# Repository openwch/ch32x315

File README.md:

# RISC-V core industrial-grade multi-channel ADC microcontroller CH32X315
EN | [中文](README_zh.md)

### Overview

CH32X315 is a multi-channel ADC microcontroller designed based on the Tibetan barley RISC-V core. The core supports 480MHz zero-wait operation and supports single-precision floating-point instructions and bit manipulation instructions. CH32X315 has four sets of high-speed 12-bit ADC conversion units built-in, providing 48 direct inputs
The channel supports scanning mode and can be expanded to 8 times the number of channels with an analog switch chip, which can automatically switch. It is equipped with a built-in USB 3.0 ultra-high-speed controller and PHY, a USB 2.0 high-speed controller and PHY, as well as a Type-C/PD controller and PHY. It supports USB 3.2 Gen1 and USBSS Device
Equipment functions, USBHS Host and USBHS Device functions, Type-C and PDUSB fast charging functions; provides rich peripheral resources such as DMA controller, ARGB single-wire RGB driver, multiple sets of timers, 4 sets of USART serial ports, 2 sets of I2C interfaces, 3 sets of SPI, etc.
CH32X305 has the USB 3.0 module removed from CH32X315.

### System Block Diagram

### Features

- Qingke 32-bit RISC-V3F core, with multiple instruction set combinations
- Fast programmable interrupt controller + hardware interrupt stack
- Level 2 interrupt nesting
- Supports single-precision floating-point instructions and bit manipulation instructions
- The highest frequency of the kernel is 480MHz, and the highest frequency of the system is 313MHz
- In performance mode, the kernel supports 625MHz, and the system supports 400MHz

- 64KB volatile data storage area SRAM
- 480KB program storage area CodeFlash
(192KB zero-wait application area + 288KB non-zero-wait data area)
- 28KB system bootloader storage area for BootLoader
- 128B user-defined information storage area

- System power supply VDD range: 2.8~3.6V
- Low power consumption modes: sleep, stop

- Built-in factory-calibrated 20MHz RC oscillator
- Built-in RC oscillator with a frequency of approximately 40kHz
- High-speed oscillator supports external 5~32MHz crystal
- Power-on/off reset, programmable voltage monitor

- One 16-bit advanced timer, supporting dead zone control and emergency braking
Vehicle, providing complementary PWM output for motor control
- 2 general-purpose 16-bit timers and 1 general-purpose 32-bit timer, providing input capture
Capture/output comparison/PWM/pulse counting and incremental encoder input
- 2 watchdog timers (independent and window type)
- System time base timer: 32-bit counter

- Real-Time Clock (RTC): 32-bit independent timer

- 11 DMA channels, supporting ring buffer management

- 4 sets of 12-bit analog-to-digital converters (ADCs):
- Analog input range: VREF- to VREF+
- 4*12=48 external signal channels + 1 internal signal channel
- Sampling rate up to 5Msps, supporting multiple ADC conversion modes
- Supports scanning mode and automatic switching with external extensions
- Support for early channel switching to facilitate stable signal sampling
- Supports 4 sets of ADC cascading, equivalent to a 20Msps sampling rate

- 4 sets of USART serial ports: support LIN

- 2 sets of I2C interfaces

- 3 sets of SPI interfaces

- 5Gbps ultra-high-speed USB 3.0 controller and PHY
- Supports ultra-high-speed Device mode
- High-speed integrated design, with a measured speed of 450 Mbytes per second

- 480Mbps high-speed USB 2.0 controller and PHY:
- Supports high-speed/full-speed Host and Device modes
- Supports 1024-byte data packets

- USB PD and Type-C controller and PHY:
- Supports DRP, Sink, and Source applications, as well as PDUSB
- Supports PD3.2 and EPR, and supports 100W or 240W fast charging

- Cascadable and addressable single-wire RGB (ARGB)

- Fast GPIO port:
- 64 I/O ports, mapped to 16 external interrupts

- CRC calculation unit, 96-bit unique chip ID

- Supports both single-line and dual-line debugging modes

- Packaging type: LQFP, QFN

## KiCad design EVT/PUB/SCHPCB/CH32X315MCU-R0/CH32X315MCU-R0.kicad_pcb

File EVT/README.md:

# EVT

### -- download URL
*  CH32X315EVT.ZIP-https://www.wch.cn/downloads/CH32X315EVT_ZIP.html

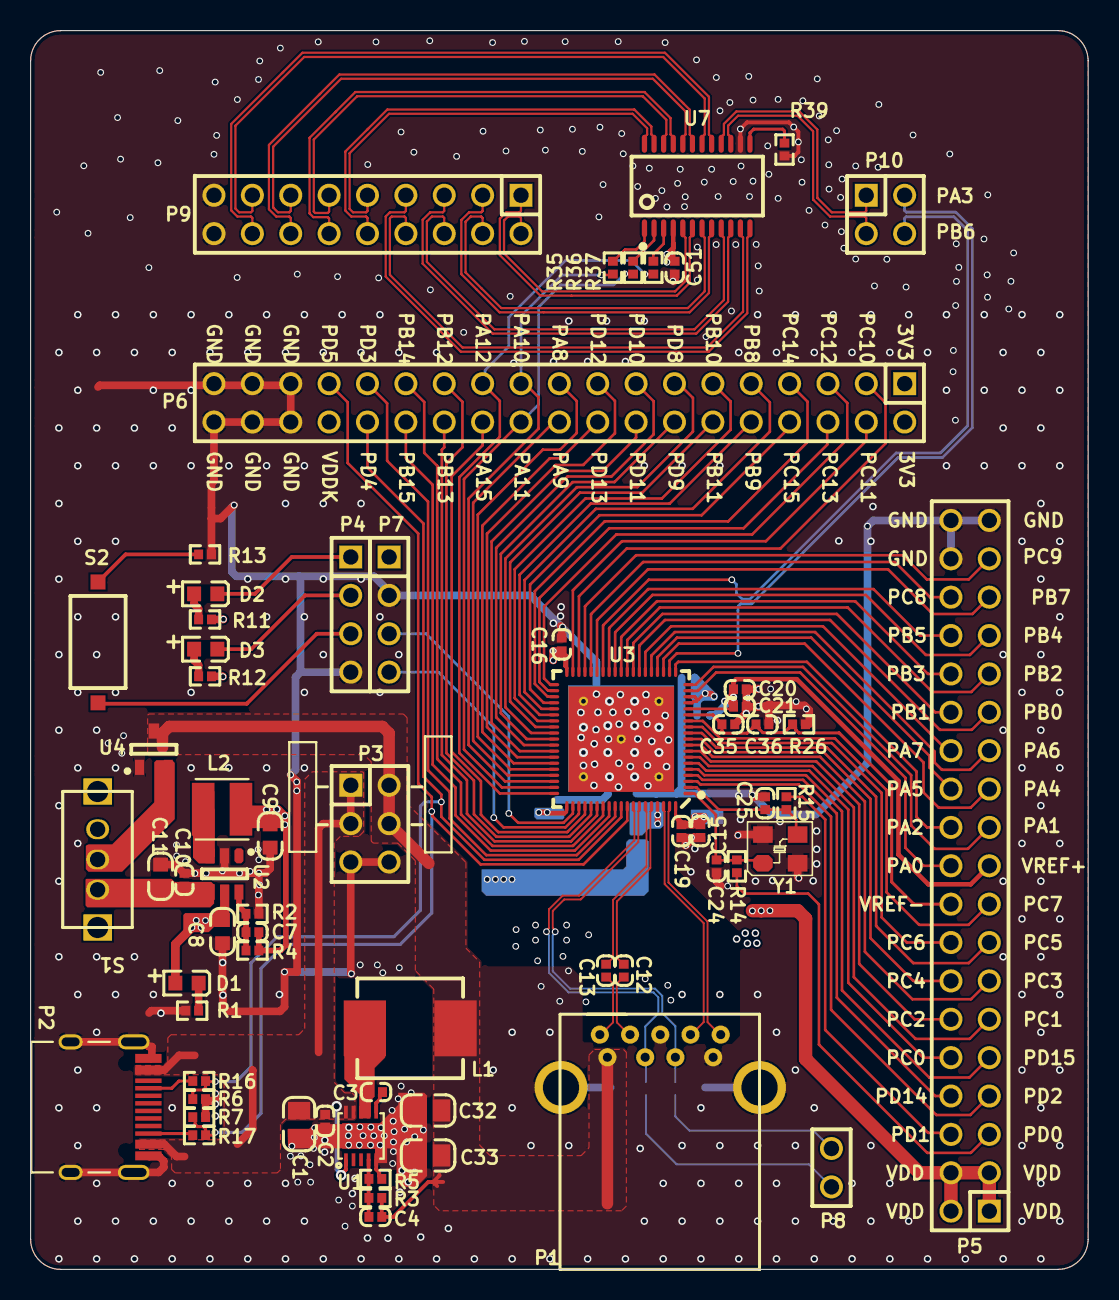
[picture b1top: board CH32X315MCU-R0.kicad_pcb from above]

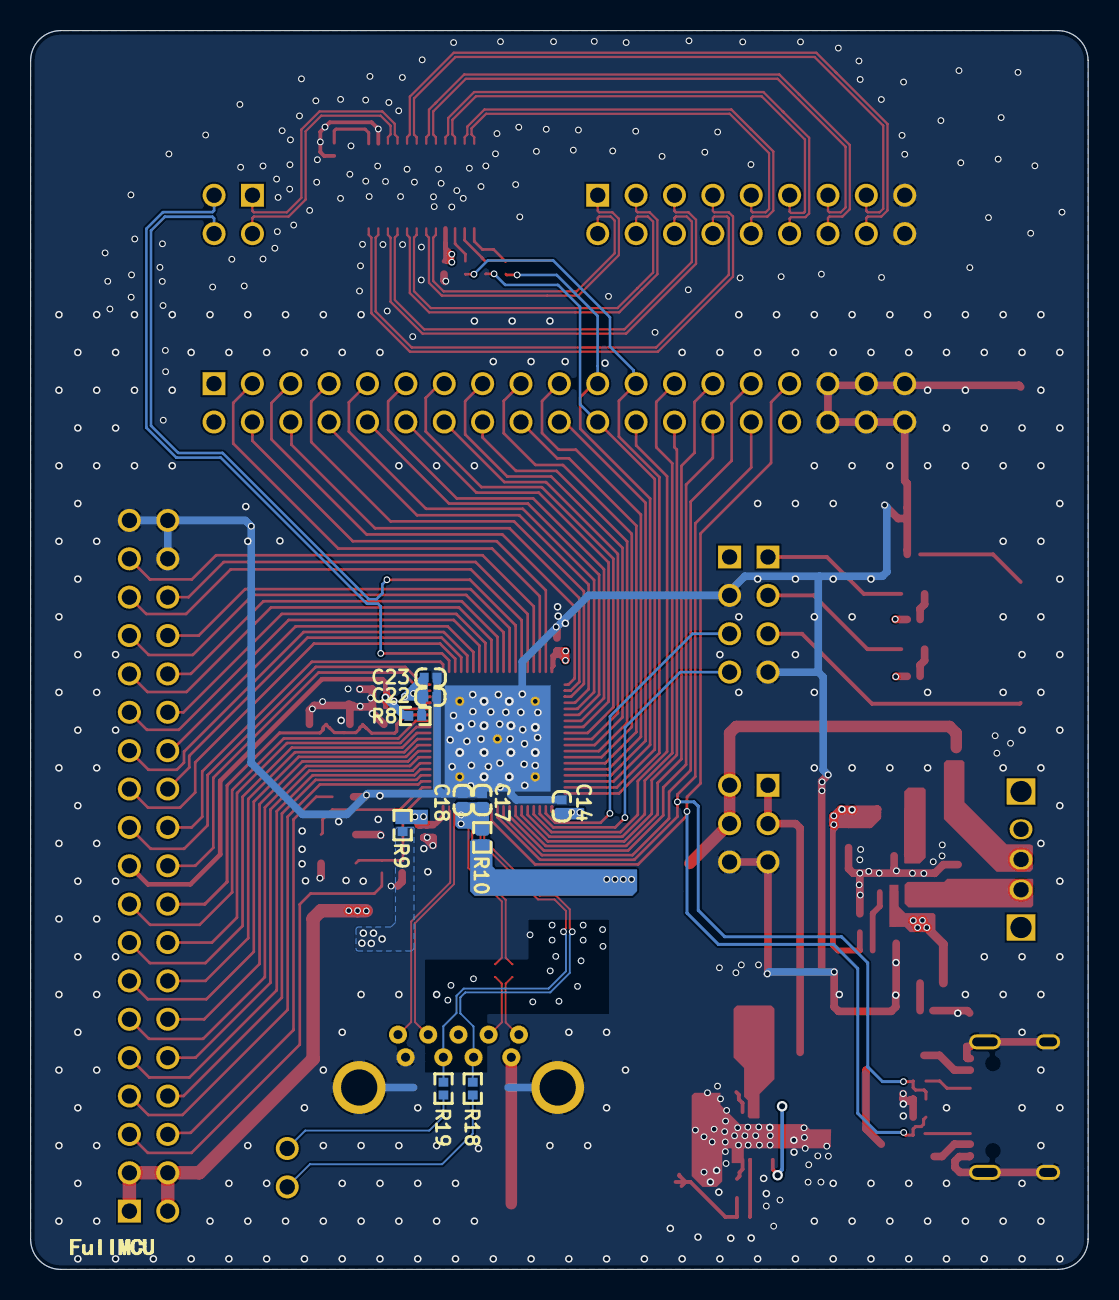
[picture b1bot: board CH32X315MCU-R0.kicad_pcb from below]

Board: 4 copper layers, 70.0 x 82.0 mm, 75 parts (10 on the bottom side), 121 nets.

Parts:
C1: NC(22uF/35V); 0805_C
C2: NC(0.1uF); 0402_C
C3: NC(100nF); 0402_C
C4: NC(68pF); 0402_C
C7: NC(4.7pF); 0402_C
C8, C11: 10uF; 0603_C
C9: NC(10uF); 0603_C
C10, C21, C51: 1uF; 0402_C
C12, C13, C14, C16, C18, C19, C22, C23: 0.1uF; 0402_C
C15: 4.7uF; 0402_C
C17: 2.2uF; 0402_C
C20: 0.01uF; 0402_C
C24, C25: 20pF; 0402_C
C32, C33: NC(22uF); 0805_C
C35: NC(0.01uF); 0402_C
C36: NC(1uF); 0402_C
D1, D3: RED; 0603+
D2: BLUE; 0603+
L1: NC(4.7uH/5A); IND-SMD_L7.0-W6.6
L2: NC(2.2uH); CD32
P1: USB3.0-A; USB3.0-A-Receptacle
P2: TYPE-C; TYPE-C-Receptacle-2.0
P3: HEADER 3x2; IDC6-2.54mm
P4, P7: HEADER 4; SIP4-2.54mm
P5, P6: HEADER 19x2; IDC38-2.54MM
P8: HEADER 2; SIP2-2.54mm
P9: HEADER 9x2; IDC18-2.54MM
P10: Header 2X2; IDC4-2.54mm
R1, R11, R12: 1K; 0402
R2, R4: NC(200k); 0402
R3: NC(15k); 0402
R5: NC(4.7k); 0402
R6, R7: NC(5.1K); 0402
R8, R9, R26: 0R; 0402
R10: NC(0R); 0402
R13: 10K; 0402
R14, R15, R16, R17, R18, R19, R35, R36, R37: NC(0Ω); 0402
R39: 0Ω; 0402
S1: SW SPDT; SW1
S2: KEY; SMD_6.1x3.65x2.5mm-KEY
U1: NC(CH2024Q); DFN10_3X3
U2: CH2003K; SOT-23-6
U3: CH32X315MCU; QFN76_9X9
U4: CH213; SOT-23-3
U7: CH448U; QSOP24
Y1: 20M; XT3225

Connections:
1V2: C7.1, C9.2, L2.2, R4.1, R10.2
3V3: C8.2, D1.1, P6.1, P6.2, P7.1, R9.1, U2.5
+5V: C10.2, C11.2, S1.3, U2.4
A0_X: P9.1, U7.6
A0_Y: P9.2, U7.5
A1_X: P9.3, U7.8
A1_Y: P9.4, U7.7
A2_X: P9.5, U7.10
A2_Y: P9.6, U7.9
A3_X: P9.7, U7.12
A3_Y: P9.8, U7.11
A4_X: P9.9, U7.24
A4_Y: P9.10, U7.23
A5_X: P9.11, U7.22
A5_Y: P9.12, U7.21
A6_X: P9.13, U7.20
A6_Y: P9.14, U7.19
A7_X: P9.15, U7.18
A7_Y: P9.16, U7.17
A_X: P10.1, U7.16
A_Y: P10.3, U7.15
CC1: P6.30, R6.1, R16.2, U3.67
CC2: P6.31, R7.1, R17.2, U3.68
EN#: R39.2, U7.13
FB: C4.2, R3.1, R5.2, U1.4
GND: C1.1, C2.1, C8.1, C9.1, C10.1, C11.1, C14.2, C15.2, C16.1, C17.2, C18.2, C19.2, C20.2, C21.2, C22.2, C23.2, C24.2, C25.2, C32.1, C33.1, C35.2, C36.2, C51.2, P1.0, P1.4, P1.7, P2.0, P2.A1, P2.B1, P3.5, P3.6, P4.4, P5.36, P5.37, P5.38, P6.33, P6.34, P6.35, P6.36, P6.37, P6.38, P7.2, P9.17, P9.18, R1.2, R2.2, R5.1, R6.2, R7.2, R13.1, R26.1, R39.1, U1.0, U1.5, U2.2, U3.0, U4.1, U7.14, Y1.2, Y1.4
KEY: P4.3, S2.1
LED1: D2.2, P4.1
LED2: D3.2, P4.2
NetC3_1: C3.1, U1.6
NetC3_2: C3.2, L1.1, U1.7, U1.8
NetC7_2: C7.2, R2.1, R4.2, U2.6
NetC12_1: C12.1, P1.8
NetC13_1: C13.1, P1.9
NetD1_2: D1.2, R1.1
NetD2_1: D2.1, R11.2
NetD3_1: D3.1, R12.2
NetL2_1: L2.1, U2.3
NetP2_A5: P2.A5, R16.1
NetP2_B5: P2.B5, R17.1
NetR13_2: R13.2, S2.2
NetS1_1: S1.1, U4.2
PA0: P5.20, U3.18
PA1: P5.21, U3.19
PA2: P5.22, U3.20
PA3: P10.2, U3.21
PA4: P5.23, U3.22
PA5: P5.24, U3.23
PA6: P5.25, U3.24
PA7: P5.26, U3.25
PA8: P6.19, U3.53
PA9: P6.20, U3.54
PA10: P6.21, R35.2, U3.55
PA11: P6.22, R36.2, U3.56
PA12: P6.23, R37.2, U3.57
PA13: P7.3, U3.59
PA14: P7.4, U3.60
PA15: P6.24, U3.61
PB0: P5.27, U3.26
PB1: P5.28, U3.27
PB2: P5.29, U3.28
PB3: P5.30, U3.29
PB4: P5.31, U3.30
PB5: P5.32, U3.31
PB6: P10.4, U3.32
PB7: P5.33, U3.33
PB8: P6.9, U3.43
PB9: P6.10, U3.44
PB10: P6.11, U3.45
PB11: P6.12, U3.46
PB12: P6.25, U3.62
PB13: P6.26, U3.63
PB14: P6.27, U3.64
PB15: P6.28, U3.65
PC0: P5.10, U3.6
PC1: P5.11, U3.7
PC2: P5.12, U3.8
PC3: P5.13, U3.9
PC4: P5.14, U3.10
PC5: P5.15, U3.11
PC6: P5.16, U3.12
PC7: P5.17, U3.13
PC8: P5.34, U3.34
PC9: P5.35, U3.35
PC10: P6.3, U3.36
PC11: P6.4, U3.37
PC12: P6.5, U3.39
PC13: P6.6, U3.40
PC14: P6.7, U3.41
PC15: P6.8, U3.42
PD0: P5.5, R14.1
PD1: P5.6, R15.1
PD2: P5.7, U3.3
PD3: P6.29, U3.66
PD6: P8.1, R18.2
PD7: P8.2, R19.2
PD8: P6.13, U3.47
PD9: P6.14, U3.48
PD10: P6.15, U3.49
PD11: P6.16, U3.50
PD12: P6.17, U3.51
PD13: P6.18, U3.52
PD14: P5.8, U3.4
PD15: P5.9, U3.5
SEL0: R35.1, U7.1
SEL1: R36.1, U7.2
SEL2: R37.1, U7.3
SSRXA: P1.5, U3.75
SSRXB: P1.6, U3.74
SSTXA: C12.2, U3.72
SSTXB: C13.2, U3.71
USBHS_DM: P1.2, R18.1, U3.69
USBHS_DP: P1.3, R19.1, U3.70
VBUS_CC: C1.2, C2.2, P2.A4, P2.B4, P3.1, P3.3, U1.1, U1.9, U1.10
VBUS_USB: C4.1, C32.2, C33.2, L1.2, P1.1, P3.2, P3.4, R3.2, U4.3
VDD: C14.1, C15.1, C16.2, C19.1, C22.1, C23.1, C51.1, P5.1, P5.2, P5.3, P5.4, R8.1, R9.2, R11.1, R12.1, U3.16, U3.17, U3.38, U3.58, U3.76, U7.4
VDDK: C17.1, C18.1, P6.32, R10.1, U3.73
VREF+: C20.1, C21.1, P5.19, R8.2, U3.15
VREF-: C35.1, C36.1, P5.18, R26.2, U3.14
XI: C24.1, R14.2, U3.1, Y1.1
XO: C25.1, R15.2, U3.2, Y1.3

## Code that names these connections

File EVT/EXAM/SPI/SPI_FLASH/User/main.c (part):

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/*
 *@Note
 SPI interface operation flash peripheral routine:
 Master:SPI1_SCK(PA5);SPI1_MISO(PA7);SPI1_MOSI(PA6).
 This example demonstrates SPI operation Winbond W25Qxx SPIFLASH.
 pins:
    CS  -- PA2
    DO  -- PA7(SPI1_MISO)
    WP   -- 3.3V
    DI   -- PA6(SPI1_MOSI)
    CLK  -- PA5(SPI1_SCK)
    HOLD -- 3.3V

*/
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    RCC_HB2PeriphClockCmd(RCC_HB2Periph_AFIO | RCC_HB2Periph_GPIOB | RCC_HB2Periph_GPIOA, ENABLE);
    RCC_HB2PeriphClockCmd(RCC_HB2Periph_SPI1, ENABLE);

    // CS PB12
    GPIO_InitStructure.GPIO_Pin   = GPIO_Pin_2;
    GPIO_InitStructure.GPIO_Speed = GPIO_Speed_Very_High;
    GPIO_InitStructure.GPIO_Mode  = GPIO_Mode_Out_PP;
    GPIO_Init(GPIOA, &GPIO_InitStructure);
    GPIO_WriteBit(GPIOA, GPIO_Pin_2, 1);

    // SPI1_SCK PA5(AF4)
    GPIO_PinAFConfig(GPIOA, GPIO_PinSource5, GPIO_AF4);
    GPIO_InitStructure.GPIO_Pin   = GPIO_Pin_5;
    GPIO_InitStructure.GPIO_Speed = GPIO_Speed_High;
    GPIO_InitStructure.GPIO_Mode  = GPIO_Mode_AF_PP;
    GPIO_Init(GPIOA, &GPIO_InitStructure);

    // SPI1_MOSI PA6(AF4)
    GPIO_PinAFConfig(GPIOA, GPIO_PinSource6, GPIO_AF4);
    GPIO_InitStructure.GPIO_Pin   = GPIO_Pin_6;
    GPIO_InitStructure.GPIO_Speed = GPIO_Speed_High;
    GPIO_InitStructure.GPIO_Mode  = GPIO_Mode_AF_PP;
    GPIO_Init(GPIOA, &GPIO_InitStructure);

    // SPI1_MISO PA7(AF4)
    GPIO_PinAFConfig(GPIOA, GPIO_PinSource7, GPIO_AF4);
    GPIO_InitStructure.GPIO_Pin  = GPIO_Pin_7;
    GPIO_InitStructure.GPIO_Mode = GPIO_Mode_IPU;
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
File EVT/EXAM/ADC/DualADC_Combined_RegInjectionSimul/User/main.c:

/********************************** (C) COPYRIGHT *******************************
* File Name          : main.c
* Author             : WCH
* Version            : V1.0.1
* Date               : 2026/10/16
* Description        : Main program body.
*********************************************************************************
* Copyright (c) 2021 Nanjing Qinheng Microelectronics Co., Ltd.
* Attention: This software (modified or not) and binary are used for 
* microcontroller manufactured by Nanjing Qinheng Microelectronics.
*******************************************************************************/

/*
* *@Note 
*  Dual ADC combined regular + injection + simultaneous sampling routine:
*  Rule group ADC1 channel 2 (PA4), ADC2 channel 4 (PA6), injection group ADC1 channel 3 (PC9) ADC2 channel 5 (PC11))
* The rule group injection groups are all triggered by software, and the dual ADC rule group data is obtained through
*  the DMA interrupt, and the dual ADC injection group data is obtained through the ADC interrupt.
*/


#include "debug.h"
/* Global Variable */
vu32 TxBuf[1];
vu16 Adc_Val[2];
vu16 ADC_Val1, ADC_Val2;
volatile u8 Injected_IT_Flag,DMA_IT_Flag;

void ADC1_IRQHandler(void)   __attribute__((interrupt("WCH-Interrupt-fast")));
void DMA1_Channel1_IRQHandler(void)   __attribute__((interrupt("WCH-Interrupt-fast")));

/*********************************************************************
 * @fn      ADC_Function_Init
 *
 * @brief   Initializes ADC collection.
 *
 * @return  none
 */
void  ADC_Function_Init(void)
{
    ADC_InitTypeDef ADC_InitStructure={0};
    GPIO_InitTypeDef GPIO_InitStructure={0};
   

	RCC_HB2PeriphClockCmd(RCC_HB2Periph_GPIOA|RCC_HB2Periph_GPIOC, ENABLE );
	RCC_HB2PeriphClockCmd(RCC_HB2Periph_ADC1, ENABLE );
	RCC_HB2PeriphClockCmd(RCC_HB2Periph_ADC2, ENABLE );
    RCC_ADCCLKSourceConfig(RCC_ADCCLKSource_HCLK);
	RCC_ADCCLKConfig(RCC_ADCPRE_Div2,RCC_PPRE2_Div8);

    GPIO_InitStructure.GPIO_Pin = GPIO_Pin_4 |GPIO_Pin_6;
    GPIO_InitStructure.GPIO_Mode = GPIO_Mode_AIN;
    GPIO_Init(GPIOA, &GPIO_InitStructure);

    GPIO_InitStructure.GPIO_Pin = GPIO_Pin_9 |GPIO_Pin_11;
    GPIO_InitStructure.GPIO_Mode = GPIO_Mode_AIN;
    GPIO_Init(GPIOC, &GPIO_InitStructure);

    ADC_DeInit(ADC1);
    ADC_DeInit(ADC2);

    ADC_InitStructure.ADC_Mode = ADC_Mode_RegInjecSimult;
    ADC_InitStructure.ADC_ScanConvMode = DISABLE;
    ADC_InitStructure.ADC_ContinuousConvMode = DISABLE;
    ADC_InitStructure.ADC_ExternalTrigConv = ADC_ExternalTrigConv_None;
    ADC_InitStructure.ADC_DataAlign = ADC_DataAlign_Right;
    ADC_InitStructure.ADC_NbrOfChannel = 1;
    ADC_InitStructure.ADC_OutputBuffer = ADC_OutputBuffer_Disable;
    ADC_Init(ADC1, &ADC_InitStructure);

	ADC_SampleTimeModeConfig(ADC1, ADC_Channel_2, ADC_Sample_Time_Mode0);
	ADC_RegularChannelConfig(ADC1, ADC_Channel_2, 1);
	ADC_SetMode0SampleTimeConfig(ADC1, ADC_Channel_2,ADC_SampleTime_CyclesMode7);


    ADC_InjectedSequencerLengthConfig(ADC1, 1);

	ADC_SampleTimeModeConfig(ADC1, ADC_Channel_3, ADC_Sample_Time_Mode0);
	ADC_InjectedChannelConfig(ADC1, ADC_Channel_3, 1);
	ADC_SetMode0SampleTimeConfig(ADC1, ADC_Channel_3,ADC_SampleTime_CyclesMode7);
    
    ADC_ExternalTrigInjectedConvConfig(ADC1,ADC_ExternalTrigInjecConv_None );

    NVIC_EnableIRQ(ADC1_IRQn);
    ADC_ITConfig(ADC1, ADC_IT_JEOC, ENABLE);
    ADC_DMACmd(ADC1, ENABLE);
    ADC_Cmd(ADC1, ENABLE);

    ADC_BufferCmd(ADC1, DISABLE);   //disable buffer
    ADC_ResetCalibration(ADC1);
    while(ADC_GetResetCalibrationStatus(ADC1));
    ADC_StartCalibration(ADC1);
    while(ADC_GetCalibrationStatus(ADC1));

    ADC_Init(ADC2, &ADC_InitStructure);

    ADC_SampleTimeModeConfig(ADC2, ADC_Channel_4, ADC_Sample_Time_Mode0);
	ADC_RegularChannelConfig(ADC2, ADC_Channel_4, 1);
	ADC_SetMode0SampleTimeConfig(ADC2, ADC_Channel_4,ADC_SampleTime_CyclesMode7);


    ADC_InjectedSequencerLengthConfig(ADC2, 1);
	ADC_SampleTimeModeConfig(ADC2, ADC_Channel_5, ADC_Sample_Time_Mode0);
	ADC_InjectedChannelConfig(ADC2, ADC_Channel_5, 1);
	ADC_SetMode0SampleTimeConfig(ADC2, ADC_Channel_5,ADC_SampleTime_CyclesMode7);

    ADC_ExternalTrigInjectedConvConfig(ADC2,ADC_ExternalTrigInjecConv_None );

    ADC_Cmd(ADC2, ENABLE);

    ADC_BufferCmd(ADC2, DISABLE);   //disable buffer
    ADC_ResetCalibration(ADC2);
    while(ADC_GetResetCalibrationStatus(ADC2));
    ADC_StartCalibration(ADC2);
    while(ADC_GetCalibrationStatus(ADC2));
}
/*********************************************************************
 * @fn      DMA_Tx_Init
 *
 * @brief   Initializes the DMAy Channelx configuration.
 *
 * @param   DMA_CHx - x can be 1 to 7.
 *          ppadr - Peripheral base address.
 *          memadr - Memory base address.
 *          bufsize - DMA channel buffer size.
 *
 * @return  none
 */
void DMA_Tx_Init( DMA_Channel_TypeDef* DMA_CHx, u32 ppadr, u32 memadr, u16 bufsize)
{
	DMA_InitTypeDef DMA_InitStructure={0};

	RCC_HBPeriphClockCmd( RCC_HBPeriph_DMA1, ENABLE );

	DMA_DeInit(DMA_CHx);
	DMA_InitStructure.DMA_PeripheralBaseAddr = ppadr;
    DMA_InitStructure.DMA_Memory0BaseAddr = memadr;
    DMA_InitStructure.DMA_DIR = DMA_DIR_PeripheralSRC;
    DMA_InitStructure.DMA_BufferSize = bufsize;
    DMA_InitStructure.DMA_PeripheralInc = DMA_PeripheralInc_Disable;
    DMA_InitStructure.DMA_MemoryInc = DMA_MemoryInc_Enable;
    DMA_InitStructure.DMA_PeripheralDataSize = DMA_PeripheralDataSize_Word;
    DMA_InitStructure.DMA_MemoryDataSize = DMA_MemoryDataSize_Word;
    DMA_InitStructure.DMA_Mode = DMA_Mode_Circular;
    DMA_InitStructure.DMA_Priority = DMA_Priority_VeryHigh;
    DMA_InitStructure.DMA_M2M = DMA_M2M_Disable;
	DMA_Init( DMA_CHx, &DMA_InitStructure );

    NVIC_EnableIRQ(DMA1_Channel1_IRQn);
    DMA_ITConfig( DMA1_Channel1, DMA_IT_TC, ENABLE );
}

/*********************************************************************
 * @fn      main
 *
 * @brief   Main program.
 *
 * @return  none
 */
int main(void)
{
    USART_Printf_Init(115200);
	SystemCoreClockUpdate();
	Delay_Init();	
	printf("SystemClk:%d\r\n",SystemCoreClock);
	printf( "ChipID:%08x\r\n",DBGMCU_GetCHIPID() );
	ADC_Function_Init();
	
	DMA_Tx_Init( DMA1_Channel1, (u32)&ADC1->RDATAR, (u32)TxBuf, 1 );
	DMA_Cmd( DMA1_Channel1, ENABLE );

	while(1)
	{
	    ADC_SoftwareStartConvCmd(ADC1, ENABLE);
        ADC_SoftwareStartConvCmd(ADC2, ENABLE);
        ADC_SoftwareStartInjectedConvCmd(ADC1, ENABLE);
        ADC_SoftwareStartInjectedConvCmd(ADC2, ENABLE);

        if(Injected_IT_Flag==1)
        {
            Injected_IT_Flag=0;
            printf( "JADC1 ch3=%04d\r\n", ADC_Val1);
            printf( "JADC2 ch5=%04d\r\n", ADC_Val2);
        }

        if(DMA_IT_Flag==1)
        {
            DMA_IT_Flag=0;
            printf("ADC1 ch2=%d\r\n",Adc_Val[0]);
            printf("ADC2 ch4=%d\r\n",Adc_Val[1]);
        }
        Delay_Ms(1000);
	}
}
/*********************************************************************
 * @fn      ADC1_IRQHandler
 *
 * @brief   This function handles ADC1  exception.
 *
 * @return  none
 */
void ADC1_IRQHandler()
{
    if(ADC_GetITStatus( ADC1, ADC_IT_JEOC)){
        Injected_IT_Flag=1;

        ADC_Val1 = ADC_GetInjectedConversionValue(ADC1, ADC_InjectedChannel_1);
        ADC_Val2 = ADC_GetInjectedConversionValue(ADC2, ADC_InjectedChannel_1);
    }
    ADC_ClearITPendingBit( ADC1, ADC_IT_JEOC);
    ADC_ClearITPendingBit( ADC2, ADC_IT_JEOC);
}

/*********************************************************************
 * @fn      DMA1_Channel1_IRQHandler
 *
 * @brief   This function handles DMA1 Channel1 exception.
 *
 * @return  none
 */
void DMA1_Channel1_IRQHandler()
{
    if(DMA_GetITStatus(DMA1_IT_TC1)==SET ){
        DMA_IT_Flag=1;
        DMA_ClearITPendingBit(DMA1_IT_GL1);

        Adc_Val[0]=TxBuf[0]&0xffff;
        Adc_Val[1]=(TxBuf[0]>>16)&0xffff;
    }
}

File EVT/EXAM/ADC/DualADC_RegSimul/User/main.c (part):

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/*
*@Note 
*Dual ADC regular simultaneous sampling routine:
*ADC1 channel 3 (PA5), ADC2 channel 3 (PC9)), ADC3 channel 3 (PD9), ADC4 channel 3 (PC1)) and the rule group channel obtains dual ADC
*conversion data through DMA interrupt.
*/

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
